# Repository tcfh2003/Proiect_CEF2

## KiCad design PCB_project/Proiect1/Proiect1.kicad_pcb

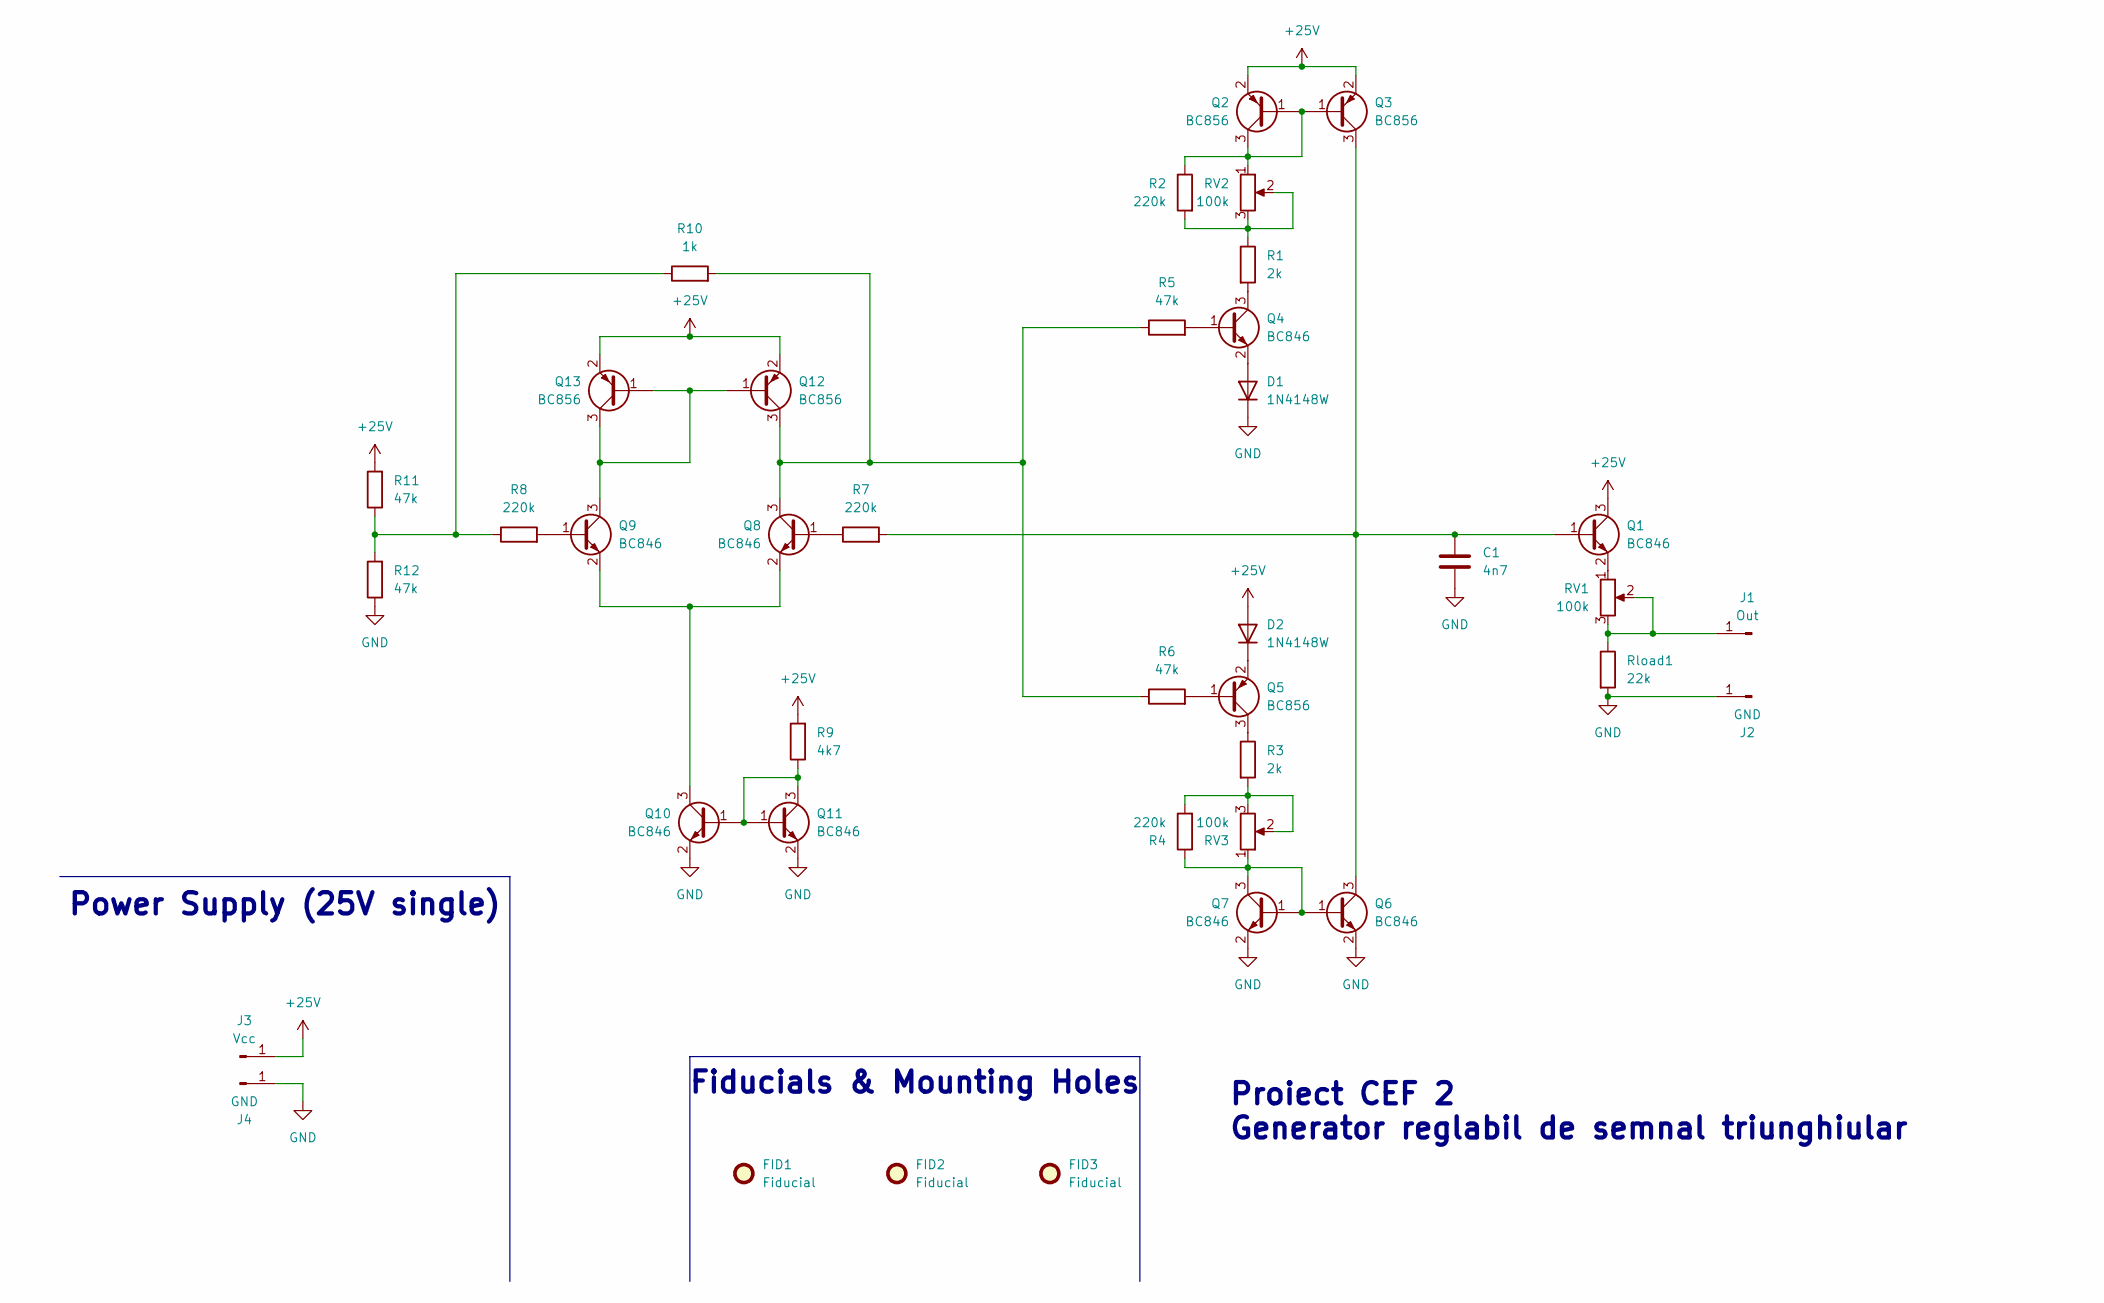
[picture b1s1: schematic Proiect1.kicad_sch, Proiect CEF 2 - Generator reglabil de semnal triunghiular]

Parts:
C1: 4n7; C_0805_2012Metric
D1, D2: 1N4148W; D_0805_2012Metric
FID1, FID2, FID3: Fiducial; Fiducial_1mm_Mask2mm
J1: Out; TestPoint_Pad_2.0x2.0mm
J2, J4: GND; TestPoint_Pad_2.0x2.0mm
J3: Vcc; TestPoint_Pad_2.0x2.0mm
Q1, Q4, Q6, Q7, Q8, Q9, Q10, Q11: BC846; SOT-23
Q2, Q3, Q5, Q12, Q13: BC856; SOT-23
R1, R3: 2k; R_0805_2012Metric
R2, R4, R7, R8: 220k; R_0805_2012Metric
R5, R6, R11, R12: 47k; R_0805_2012Metric
R9: 4k7; R_0805_2012Metric
R10: 1k; R_0805_2012Metric
RV1, RV2, RV3: 100k; Potentiometer_Vishay_TS53YL_Vertical
Rload1: 22k; R_0805_2012Metric

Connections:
+25V: D2.2 (A), J3.1, Q1.3 (C), Q2.2 (E), Q3.2 (E), Q12.2 (E), Q13.2 (E), R9.2, R11.2
GND: C1.2, D1.1 (K), J2.1, J4.1, Q6.2 (E), Q7.2 (E), Q10.2 (E), Q11.2 (E), R12.1, Rload1.2
unnamed: D1.2 (A), Q4.2 (E)
unnamed: D2.1 (K), Q5.2 (E)
unnamed: J1.1, RV1.2, RV1.3, Rload1.1
unnamed: C1.1, Q1.1 (B), Q3.3 (C), Q6.3 (C), R7.2
unnamed: Q1.2 (E), RV1.1
unnamed: Q2.1 (B), Q2.3 (C), Q3.1 (B), R2.1, RV2.1
unnamed: Q4.1 (B), R5.2
unnamed: Q4.3 (C), R1.2
unnamed: Q5.1 (B), R6.2
unnamed: Q5.3 (C), R3.1
unnamed: Q6.1 (B), Q7.1 (B), Q7.3 (C), R4.1, RV3.1
unnamed: Q8.1 (B), R7.1
unnamed: Q9.1 (B), R8.2
unnamed: Q10.1 (B), Q11.1 (B), Q11.3 (C), R9.1
unnamed: Q8.2 (E), Q9.2 (E), Q10.3 (C)
unnamed: Q9.3 (C), Q12.1 (B), Q13.1 (B), Q13.3 (C)
unnamed: Q8.3 (C), Q12.3 (C), R5.1, R6.1, R10.2
unnamed: R1.1, R2.2, RV2.2, RV2.3
unnamed: R3.2, R4.2, RV3.2, RV3.3
unnamed: R8.1, R10.1, R11.1, R12.2

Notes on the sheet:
Power Supply (25V single)
Proiect CEF 2 Generator reglabil de semnal triunghiular
Fiducials & Mounting Holes

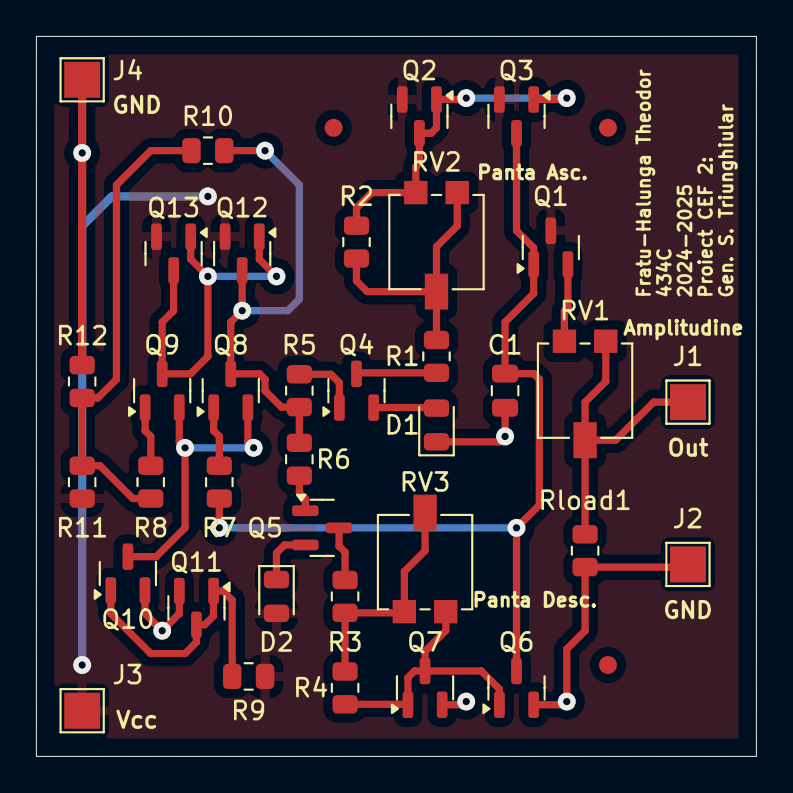
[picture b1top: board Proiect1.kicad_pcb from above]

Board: 2 copper layers, 40.0 x 40.0 mm, 39 parts (0 on the bottom side), 22 nets.

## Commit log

2024-10-12 First commit
    So far tried to use a square wave oscillator with an integrator after it and two current sources going into a capacitor, which toggle on and off alternatingly via a Schmitt trigger / Hysteresis Compa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
2024-10-12 MOSFET Schmitt Trigger works better than BJT one
2024-10-12 Proiect1_v3 now works via a Schmitt Trigger / Hysteresis Comparator made from MOSFETS
2024-10-12 As far as I can see, project is done
    Added a final common drain source follower. Amplitude control is done by a voltage divider, probably using a 100k potentiometer. Frequency and simmetry control will be done using two 25k potentiomete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
2024-10-12 Changed value of capacitor from 10nF to 2nF
    Did so in order to lower the current, therefore lowering the maximum and average power dissipation of the current source mosfets from 200mW to about 50mW, keeping well within the 330mW maximum power 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
    Another added benefit of the previous addition is that now I can use 100kOhm potentiometers for the current sources as well, meaning that there are fewer different parts to get.
    Also added temperature analysis, the only thing that seems to happen is that as temperature increases, the frequency of oscillation also increases slightly. Eyeballing it, I'd say it's less than a 10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
2024-10-18 Created a file to test op-amp circuits
    Might want to make the comparator in my triangle oscillator circuit a bit more like a real op-amp in the future.
2024-10-19 Tried to use the integrator idea instead, but it's very finicky
2024-10-19 Moved all simulation files in SPICE_simulations folder
2024-10-19 Created the PCB for the project
2024-10-29 Changed the circuit so that it's BJT based
    Using BC846B and BC856B BJT transistors. Also had to add some resistors and some 1N4148 diodes. Will see what else changed later.
2024-10-29 Changed the potentiometer values for the BJT version
2024-10-29 Standardized some of the component values
2024-10-29 Started new PCB
2024-10-29 Finished PCB
2024-10-31 Added 3d models to potentiometers
2024-11-13 Updated PCB to conform with Manufacturing Requirements
    Changed trace widths form 20 mils to 16 mils. Changed via sizes from 0.5mm/1mm to 0.4mm/1mm. Changed edge clearance from 0.5mm to 1mm. Changed trace clearance from 5? mils to 14 mils. Added 3 fiducia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
    Still need to see what is up with that MECHANIC layer. Need to generate a mechanical drawing for the board edge, a drill drawing, a drill table and a drill legend as well as a layer stackup (technica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
2024-11-29 Changed jumpers from THT to SMD
2024-11-29 Changed some of the power traces from 16 mil to 18 mil
2024-11-29 Changed reference designators J3, J4 to J2, J3
2024-11-29 Added Drill Table and simple stackup table
2024-12-08 Changed footprints of header pins for Power and Output
2024-12-08 Changed Drill Map and Drill Table to fit current layout
    Also added a .gitignore file. A bit late for this right now, but better late than never. Maybe one day I'll actually learn to include this at the start of projects instead of the end of them :/
2024-12-08 Delete PCB_project/Proiect1/Proiect1-backups directory
    This doesn't need to stay here on GitHub. If I had actually remembered to add that .gitignore file at the start, these wouldn't even be here.
2024-12-08 Fixed some alignment issues
2024-12-08 Created Gerber files
    Also moved the stackup and the drill map on the same layer, because apparently KiCad can't export multiple layers in the same Gerber file.
2024-12-13 Added final archive of project
    Archive contains Gerber Files, drawings of the KiCAD schematic, images of the PCB in KiCAD PCBView and KiCAD 3DView, Block Diagram, Simulation Waveforms, LTspice simulation file and transistor librar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
    Will also need to add the Technical Documentation later on, in which I explain exactly how the circuit is supposed to function, how it's supposed to be supplied as well as collage all the aforementio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
2024-12-25 Completed documentation
2024-12-25 Archived new complete project
2024-12-28 Fixed typos in documentation
2024-12-28 More typos
